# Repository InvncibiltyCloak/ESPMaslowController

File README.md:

# ESPMaslowController
Upgrade of the Maslow CNC controller based on the ESP32 microcontroller.

The design files are for KiCAD.

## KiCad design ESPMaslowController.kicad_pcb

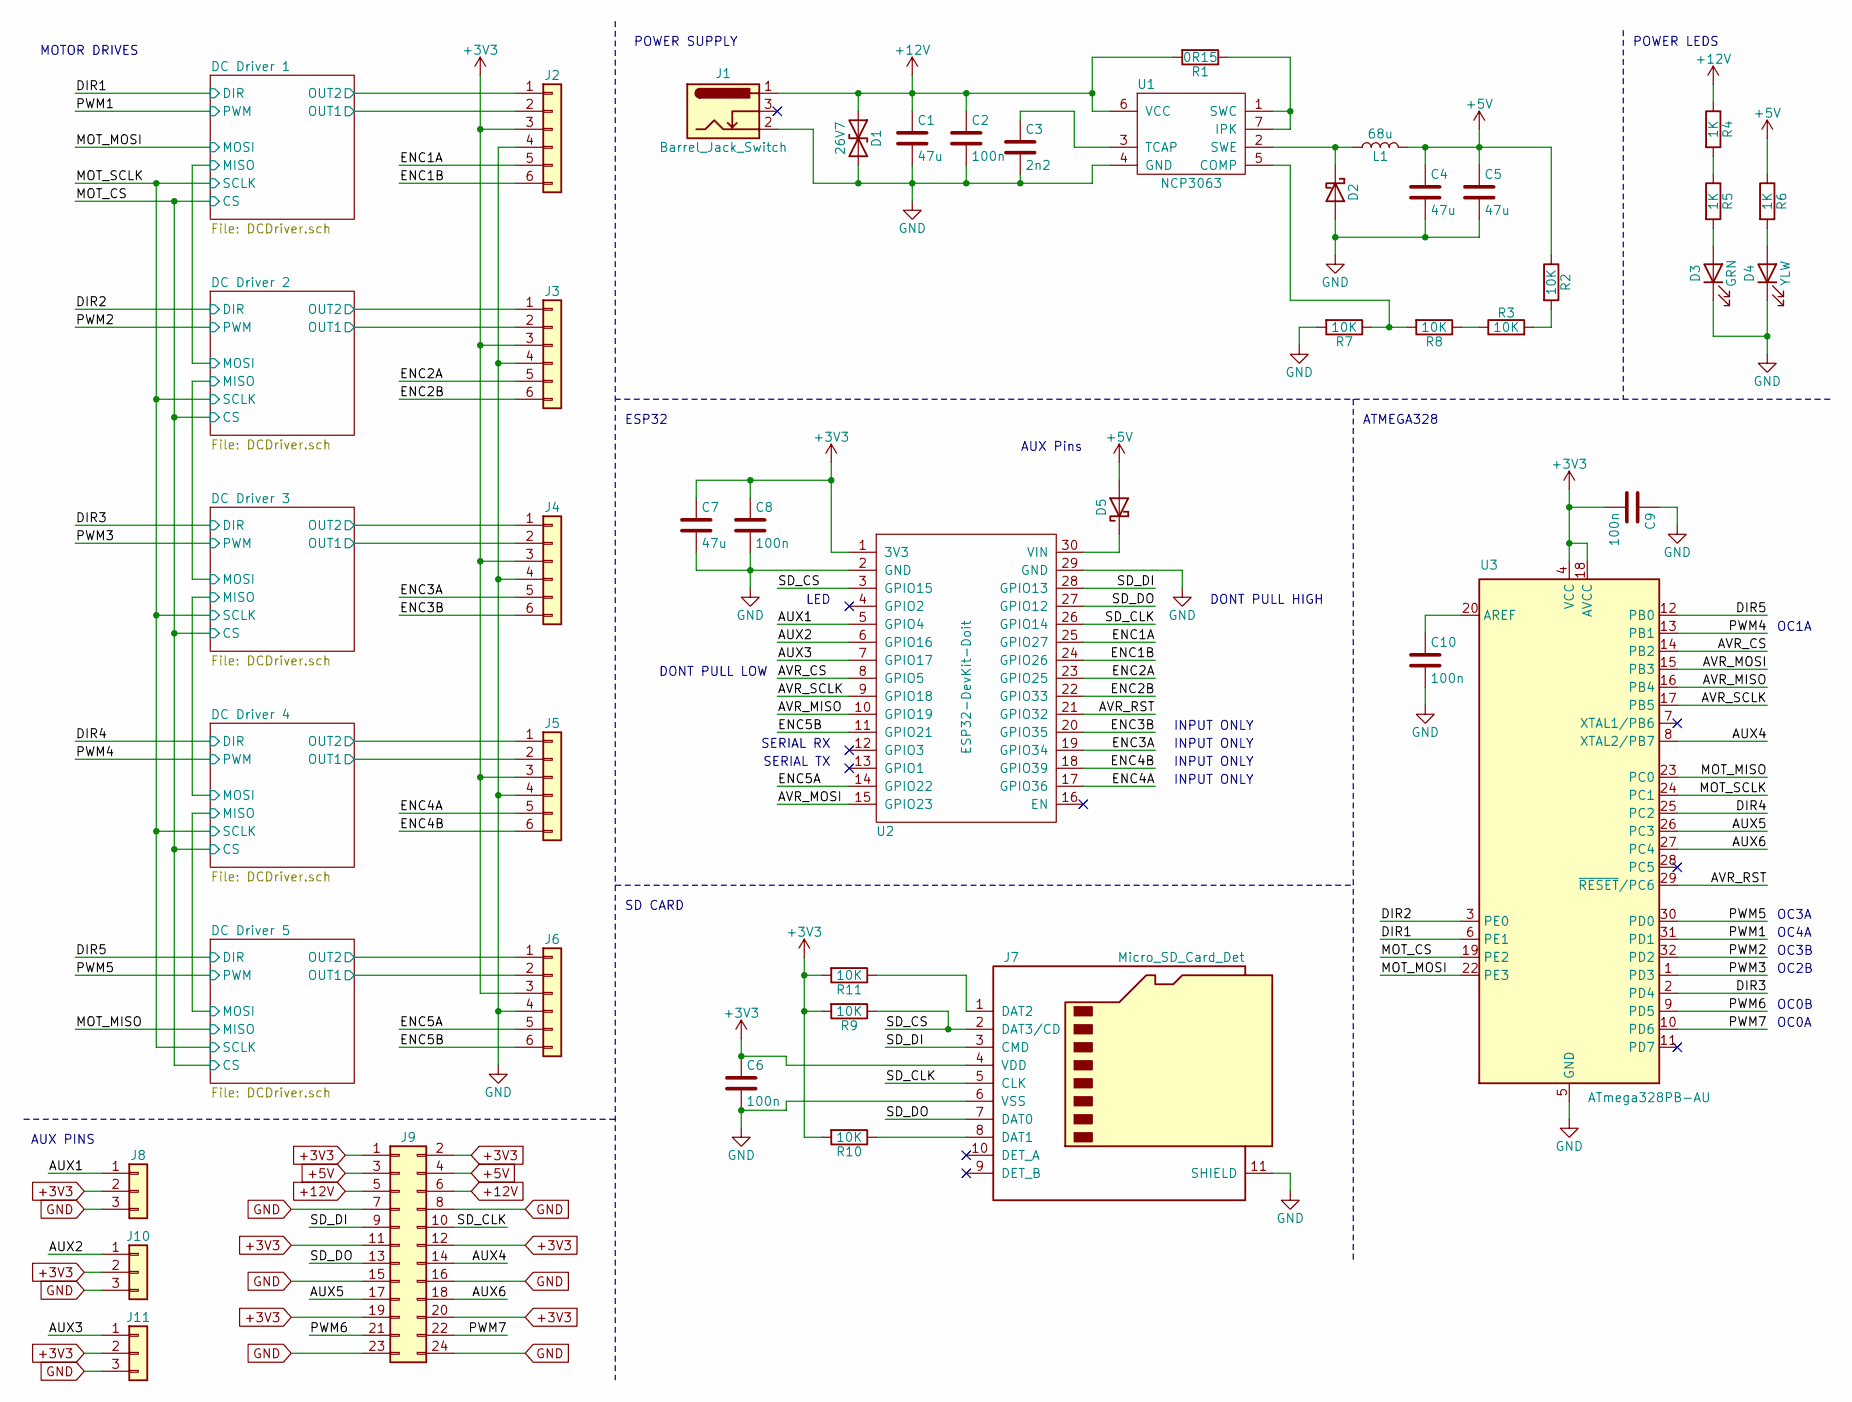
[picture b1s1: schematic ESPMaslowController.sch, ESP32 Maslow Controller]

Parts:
C1: 47u; CP_Elec_6.3x5.9; MPN 35SVPK47M
C2, C6, C8, C9, C10: 100n; C_0805_2012Metric; MPN CC0805KRX7R9BB104; LCSC C49678
C3: 2n2; C_0805_2012Metric; MPN CL21B222KBANNNC; LCSC C28260
C4, C5, C7: 47u; C_1206_3216Metric; MPN CL31A476MQHNNNE; LCSC C96123
D1: 26V7; D_SMA; MPN SMAJ24CA
D2, D5: 2A; D_SMA; MPN STPS2L30A
D3: GRN; LED_0805_2012Metric_Castellated; MPN LTST-C170KGKT; LCSC C2297
D4: YLW; LED_0805_2012Metric_Castellated; MPN LTST-C171KSKT; LCSC C2296
J1: Barrel_Jack_Switch; BarrelJack_CUI_PJ-036AH-SMT_Horizontal; MPN PJ-036AH-SMT-TR
J2, J3, J4, J5, J6: B6B-XH-A; JST_XH_B6B-XH-A_1x06_P2.50mm_Vertical; MPN B6B-PH-K-S(LF)(SN)
J7: Micro_SD_Card_Det; microSD_HC_Hirose_DM3AT-SF-PEJM5; MPN DM3AT-SF-PEJM5
J8, J10, J11: Conn_01x03; PinHeader_1x03_P2.54mm_Vertical; MPN G800W305018EU
J9: Conn_02x12_Odd_Even; PinHeader_2x12_P2.54mm_Vertical; MPN G800W590018EU
L1: 68u; L_12x12mm_H8mm; MPN NS12575T680MN
R1: 0R15; R_0805_2012Metric; MPN KDV08FR150ET
R2, R3, R7, R8, R9, R10, R11: 10K; R_0805_2012Metric; MPN RC0805FR-0710KL; LCSC C17414
R4, R5, R6: 1K; R_0805_2012Metric; MPN RC0805FR-071KL; LCSC C17513
U1: NCP3063; SO-8_3.9x4.9mm_P1.27mm; MPN NCP3063BDR2G
U2: ESP32-DevKit-Doit; ESP32-DEVKIT-V1; MPN ESP32 DevKit v1
U3: ATmega328PB-AU; TQFP-32_7x7mm_P0.8mm; MPN ATMEGA328PB-AU

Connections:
+3V3: C6.1, C7.1, C8.1, C9.2, J2.3, J3.3, J4.3, J5.3, J6.3, J7.4 (VDD), J8.2, J9.1, J9.2, J9.11, J9.12, J9.19, J9.20, J10.2, J11.2, R9.2, R10.2, R11.2, U2.1 (3V3), U3.4 (VCC), U3.18 (AVCC); also elsewhere on the board
+5V: C4.1, C5.1, D5.2 (A), J9.3, J9.4, L1.1, R2.1, R6.1
+12V: C1.1, C2.1, D1.1 (A1), J1.1, J9.5, J9.6, R1.2, R4.1, U1.6 (VCC); also elsewhere on the board
/AUX1: J8.1, U2.5 (GPIO4)
/AUX2: J10.1, U2.6 (GPIO16)
/AUX3: J11.1, U2.7 (GPIO17)
/AUX4: J9.14, U3.8 (XTAL2/PB7)
/AUX5: J9.17, U3.26 (PC3)
/AUX6: J9.18, U3.27 (PC4)
/AVR_CS: U2.8 (GPIO5), U3.14 (PB2)
/AVR_MISO: U2.10 (GPIO19), U3.16 (PB4)
/AVR_MOSI: U2.15 (GPIO23), U3.15 (PB3)
/AVR_RST: U2.21 (GPIO32), U3.29 (~RESET~/PC6)
/AVR_SCLK: U2.9 (GPIO18), U3.17 (PB5)
/DC Driver 1/OUT1: J2.2; also elsewhere on the board
/DC Driver 1/OUT2: J2.1; also elsewhere on the board
/DC Driver 2/OUT1: J3.2; also elsewhere on the board
/DC Driver 2/OUT2: J3.1; also elsewhere on the board
/DC Driver 3/OUT1: J4.2; also elsewhere on the board
/DC Driver 3/OUT2: J4.1; also elsewhere on the board
/DC Driver 4/OUT1: J5.2; also elsewhere on the board
/DC Driver 4/OUT2: J5.1; also elsewhere on the board
/DC Driver 5/OUT1: J6.2; also elsewhere on the board
/DC Driver 5/OUT2: J6.1; also elsewhere on the board
/DIR1: U3.6 (PE1); also elsewhere on the board
/DIR2: U3.3 (PE0); also elsewhere on the board
/DIR3: U3.2 (PD4); also elsewhere on the board
/DIR4: U3.25 (PC2); also elsewhere on the board
/DIR5: U3.12 (PB0); also elsewhere on the board
/ENC1A: J2.5, U2.25 (GPIO27)
/ENC1B: J2.6, U2.24 (GPIO26)
/ENC2A: J3.5, U2.23 (GPIO25)
/ENC2B: J3.6, U2.22 (GPIO33)
/ENC3A: J4.5, U2.19 (GPIO34)
/ENC3B: J4.6, U2.20 (GPIO35)
/ENC4A: J5.5, U2.17 (GPIO36)
/ENC4B: J5.6, U2.18 (GPIO39)
/ENC5A: J6.5, U2.14 (GPIO22)
/ENC5B: J6.6, U2.11 (GPIO21)
/MOT_CS: U3.19 (PE2); also elsewhere on the board
/MOT_MISO: U3.23 (PC0); also elsewhere on the board
/MOT_MOSI: U3.22 (PE3); also elsewhere on the board
/MOT_SCLK: U3.24 (PC1); also elsewhere on the board
/PWM1: U3.31 (PD1); also elsewhere on the board
/PWM2: U3.32 (PD2); also elsewhere on the board
/PWM3: U3.1 (PD3); also elsewhere on the board
/PWM4: U3.13 (PB1); also elsewhere on the board
/PWM5: U3.30 (PD0); also elsewhere on the board
/PWM6: J9.21, U3.9 (PD5)
/PWM7: J9.22, U3.10 (PD6)
/SD_CLK: J7.5 (CLK), J9.10, U2.26 (GPIO14)
/SD_CS: J7.2 (DAT3/CD), R9.1, U2.3 (GPIO15)
/SD_DI: J7.3 (CMD), J9.9, U2.28 (GPIO13)
/SD_DO: J7.7 (DAT0), J9.13, U2.27 (GPIO12)
GND: C1.2, C2.2, C3.2, C4.2, C5.2, C6.2, C7.2, C8.2, C9.1, C10.2, D1.2 (A2), D2.2 (A), D3.1 (K), D4.1 (K), J1.2, J2.4, J3.4, J4.4, J5.4, J6.4, J7.6 (VSS), J7.11 (SHIELD), J8.3, J9.7, J9.8, J9.15, J9.16, J9.23, J9.24, J10.3, J11.3, R7.2, U1.4 (GND), U2.2 (GND), U2.29 (GND), U3.5 (GND), U3.21 (GND); also elsewhere on the board
unnamed: C3.1, U1.3 (TCAP)
unnamed: C10.1, U3.20 (AREF)
unnamed: D2.1 (K), L1.2, U1.2 (SWE)
unnamed: D3.2 (A), R5.2
unnamed: D4.2 (A), R6.2
unnamed: D5.1 (K), U2.30 (VIN)
unnamed: J7.1 (DAT2), R11.1
unnamed: J7.8 (DAT1), R10.1
unnamed: R1.1, U1.1 (SWC), U1.7 (IPK)
unnamed: R2.2, R3.2
unnamed: R3.1, R8.1
unnamed: R4.2, R5.1
unnamed: R7.1, R8.2, U1.5 (COMP)

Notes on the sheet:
AUX Pins
SERIAL TX
DONT PULL LOW
INPUT ONLY
SERIAL RX
LED
DONT PULL HIGH
AUX PINS
MOTOR DRIVES
POWER SUPPLY
POWER LEDS
ESP32
ATMEGA328
SD CARD
OC2B
OC0B
OC0A
OC1A
OC3A
OC4A
OC3B

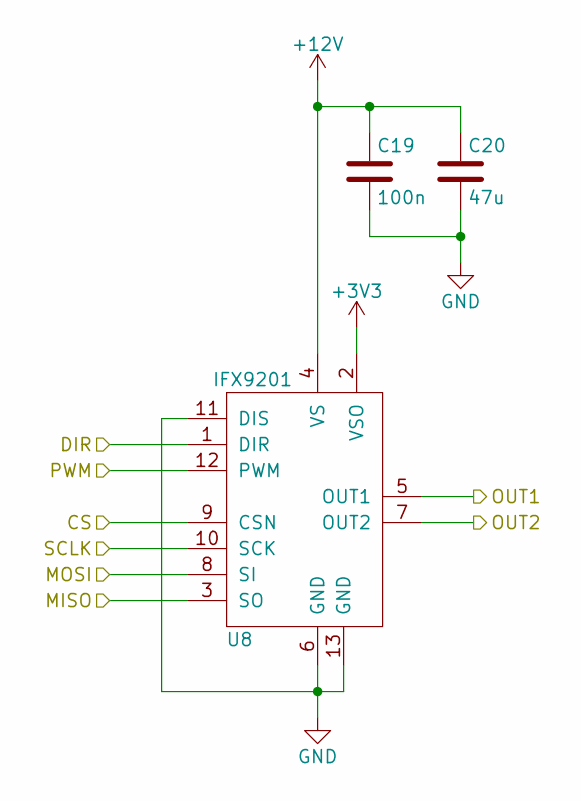
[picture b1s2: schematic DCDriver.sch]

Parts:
C11: 100n; C_0805_2012Metric; MPN CC0805KRX7R9BB104; LCSC C49678
C12: 47u; CP_Elec_6.3x5.9; MPN 35SVPK47M
U4: IFX9201; Infineon_PG-DSO-12-9_ThermalVias; MPN IFX9201SGAUMA1; LCSC C112633

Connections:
+3V3: U4.2 (VSO); also elsewhere on the board
+12V: C11.1, C12.1, U4.4 (VS); also elsewhere on the board
/DC Driver 1/MISO: U4.3 (SO); also elsewhere on the board
/DC Driver 1/OUT1: U4.5 (OUT1); also elsewhere on the board
/DC Driver 1/OUT2: U4.7 (OUT2); also elsewhere on the board
/DIR1: U4.1 (DIR); also elsewhere on the board
/MOT_CS: U4.9 (CSN); also elsewhere on the board
/MOT_MOSI: U4.8 (SI); also elsewhere on the board
/MOT_SCLK: U4.10 (SCK); also elsewhere on the board
/PWM1: U4.12 (PWM); also elsewhere on the board
GND: C11.2, C12.2, U4.6 (GND), U4.11 (DIS), U4.13 (GND); also elsewhere on the board

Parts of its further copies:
C13, C15, C17, C19: 100n; C_0805_2012Metric; MPN CC0805KRX7R9BB104; LCSC C49678
C14, C16, C18, C20: 47u; CP_Elec_6.3x5.9; MPN 35SVPK47M
U5, U6, U7, U8: IFX9201; Infineon_PG-DSO-12-9_ThermalVias; MPN IFX9201SGAUMA1; LCSC C112633

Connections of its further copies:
+3V3: U5.2 (VSO), U6.2 (VSO), U7.2 (VSO), U8.2 (VSO); also elsewhere on the board
+12V: C13.1, C14.1, C15.1, C16.1, C17.1, C18.1, C19.1, C20.1, U5.4 (VS), U6.4 (VS), U7.4 (VS), U8.4 (VS); also elsewhere on the board
/DC Driver 1/MISO: U5.8 (SI); also elsewhere on the board
/DC Driver 2/MISO: U5.3 (SO), U6.8 (SI)
/DC Driver 2/OUT1: U5.5 (OUT1); also elsewhere on the board
/DC Driver 2/OUT2: U5.7 (OUT2); also elsewhere on the board
/DC Driver 3/MISO: U6.3 (SO), U7.8 (SI)
/DC Driver 3/OUT1: U6.5 (OUT1); also elsewhere on the board
/DC Driver 3/OUT2: U6.7 (OUT2); also elsewhere on the board
/DC Driver 4/MISO: U7.3 (SO), U8.8 (SI)
/DC Driver 4/OUT1: U7.5 (OUT1); also elsewhere on the board
/DC Driver 4/OUT2: U7.7 (OUT2); also elsewhere on the board
/DC Driver 5/OUT1: U8.5 (OUT1); also elsewhere on the board
/DC Driver 5/OUT2: U8.7 (OUT2); also elsewhere on the board
/DIR2: U5.1 (DIR); also elsewhere on the board
/DIR3: U6.1 (DIR); also elsewhere on the board
/DIR4: U7.1 (DIR); also elsewhere on the board
/DIR5: U8.1 (DIR); also elsewhere on the board
/MOT_CS: U5.9 (CSN), U6.9 (CSN), U7.9 (CSN), U8.9 (CSN); also elsewhere on the board
/MOT_MISO: U8.3 (SO); also elsewhere on the board
/MOT_SCLK: U5.10 (SCK), U6.10 (SCK), U7.10 (SCK), U8.10 (SCK); also elsewhere on the board
/PWM2: U5.12 (PWM); also elsewhere on the board
/PWM3: U6.12 (PWM); also elsewhere on the board
/PWM4: U7.12 (PWM); also elsewhere on the board
/PWM5: U8.12 (PWM); also elsewhere on the board
GND: C13.2, C14.2, C15.2, C16.2, C17.2, C18.2, C19.2, C20.2, U5.6 (GND), U5.11 (DIS), U5.13 (GND), U6.6 (GND), U6.11 (DIS), U6.13 (GND), U7.6 (GND), U7.11 (DIS), U7.13 (GND), U8.6 (GND), U8.11 (DIS), U8.13 (GND); also elsewhere on the board

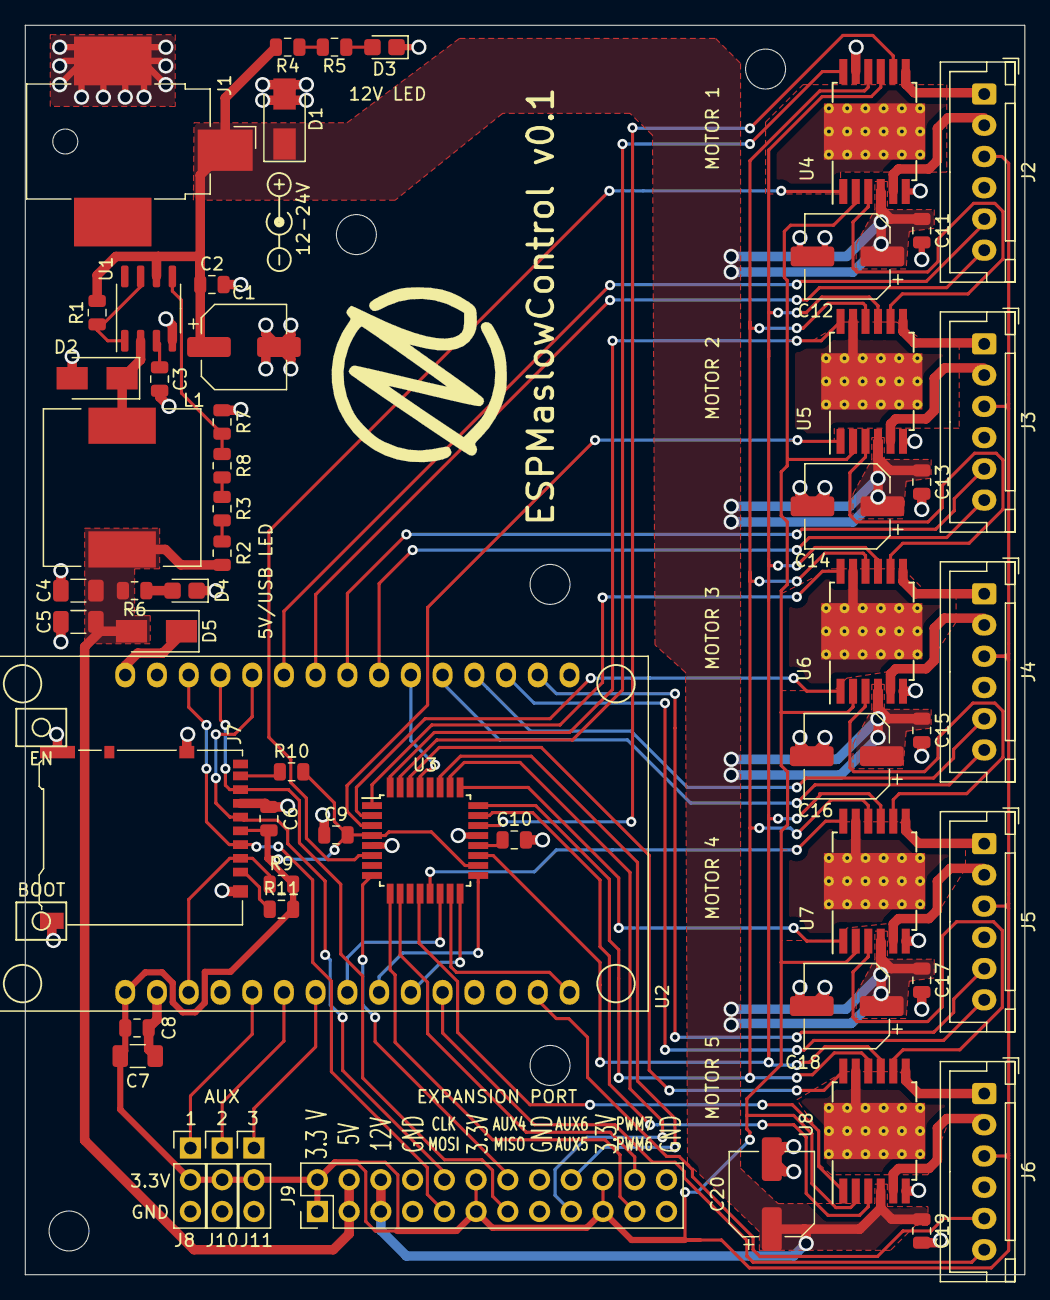
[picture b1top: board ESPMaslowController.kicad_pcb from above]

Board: 2 copper layers, 80.0 x 100.0 mm, 56 parts (0 on the bottom side), 72 nets.

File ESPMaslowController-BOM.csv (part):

Reference, Value, Footprint, Datasheet, BuyLink, MFR, MPN, Price, LCSC
"U2","ESP32-DevKit-Doit","ProjectFootprints:ESP32-DEVKIT-V1","","https://www.aliexpress.com/item/4000111107743.html","Espressif","ESP32 DevKit v1","6.00",""
"J1","Barrel_Jack_Switch","Connector_BarrelJack:BarrelJack_CUI_PJ-036AH-SMT_Horizontal","https://www.cuidevices.com/product/resource/digikeypdf/pj-03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","","CUI","PJ-036AH-SMT-TR","1.36",""
"J7","Micro_SD_Card_Det","Connector_Card:microSD_HC_Hirose_DM3AT-SF-PEJM5","https://www.hirose.com/product/document?clcode=CL0609-0033-6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","","HRS","DM3AT-SF-PEJM5","2.50",""
"C6","100n","Capacitor_SMD:C_0805_2012Metric","https://www.yageo.com/upload/media/product/productsearch/dat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","","Yageo","CC0805KRX7R9BB104","0.046","C49678"
"C8","100n","Capacitor_SMD:C_0805_2012Metric","https://www.yageo.com/upload/media/product/productsearch/dat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","","Yageo","CC0805KRX7R9BB104","0.046","C49678"
"C2","100n","Capacitor_SMD:C_0805_2012Metric","https://www.yageo.com/upload/media/product/productsearch/dat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","","Yageo","CC0805KRX7R9BB104","0.046","C49678"
"C1","47u","Capacitor_SMD:CP_Elec_6.3x5.9","https://industrial.panasonic.com/cdbs/www-data/pdf/AAB8000/A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","","Panasonic","35SVPK47M","0.713",""
"U1","NCP3063","Package_SO:SO-8_3.9x4.9mm_P1.27mm","http://www.onsemi.com/pub/Collateral/NCP3063-D.PDF","","ONSemi","NCP3063BDR2G","0.99",""
"C3","2n2","Capacitor_SMD:C_0805_2012Metric","http://www.samsungsem.com/kr/support/product-search/mlcc/CL2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","","Samsung","CL21B222KBANNNC","0.10","C28260"
"R1","0R15","Resistor_SMD:R_0805_2012Metric","https://www.ohmite.com/assets/docs/res_kdv.pdf?r=false","","Ohmite","KDV08FR150ET","0.29",""
"R2","10K","Resistor_SMD:R_0805_2012Metric","https://www.yageo.com/upload/media/product/productsearch/dat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","","Yageo","RC0805FR-0710KL","0.10","C17414"
"L1","68u","Inductor_SMD:L_12x12mm_H8mm","https://ds.yuden.co.jp/TYCOMPAS/ut/detail?pn=NS12575T680MN%20&u=M","","Taiyo Yuden","NS12575T680MN","1.47",""
"D2","2A","Diode_SMD:D_SMA","https://datasheet.lcsc.com/szlcsc/STMicroelectronics-STPS2L3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","","STMicro","STPS2L30A","0.43",""
"C4","47u","Capacitor_SMD:C_1206_3216Metric","https://media.digikey.com/pdf/Data%20Sheets/Samsung%20PDFs/C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","","Samsung","CL31A476MQHNNNE","0.33","C96123"
"C5","47u","Capacitor_SMD:C_1206_3216Metric","https://media.digikey.com/pdf/Data%20Sheets/Samsung%20PDFs/C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","","Samsung","CL31A476MQHNNNE","0.33","C96123"
"C7","47u","Capacitor_SMD:C_1206_3216Metric","https://media.digikey.com/pdf/Data%20Sheets/Samsung%20PDFs/C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","","Samsung","CL31A476MQHNNNE","0.33","C96123"
"J2","B6B-PH-K-S","Connector_JST:JST_PH_B6B-PH-K_1x06_P2.00mm_Vertical","http://www.jst-mfg.com/product/pdf/eng/ePH.pdf","","JST","B6B-PH-K-S(LF)(SN)","0.33",""
"J3","B6B-PH-K-S","Connector_JST:JST_PH_B6B-PH-K_1x06_P2.00mm_Vertical","http://www.jst-mfg.com/product/pdf/eng/ePH.pdf","","JST","B6B-PH-K-S(LF)(SN)","0.33",""
"J4","B6B-PH-K-S","Connector_JST:JST_PH_B6B-PH-K_1x06_P2.00mm_Vertical","http://www.jst-mfg.com/product/pdf/eng/ePH.pdf","","JST","B6B-PH-K-S(LF)(SN)","0.33",""
"D5","2A","Diode_SMD:D_SMA","https://datasheet.lcsc.com/szlcsc/STMicroelectronics-STPS2L3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","","STMicro","STPS2L30A","0.43",""
"D3","GRN","LED_SMD:LED_0805_2012Metric_Castellated","http://optoelectronics.liteon.com/upload/download/DS22-2000-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","","Lite-On","LTST-C170KGKT","0.35","C2297"
"R5","1K","Resistor_SMD:R_0805_2012Metric","https://www.yageo.com/upload/media/product/productsearch/dat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","","Yageo","RC0805FR-071KL","0.10","C17513"
"R4","1K","Resistor_SMD:R_0805_2012Metric","https://www.yageo.com/upload/media/product/productsearch/dat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","","Yageo","RC0805FR-071KL","0.10","C17513"
"D4","YLW","LED_SMD:LED_0805_2012Metric_Castellated","http://optoelectronics.liteon.com/upload/download/DS22-2000-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","","Lite-On","LTST-C171KSKT","0.31","C2296"
"R6","1K","Resistor_SMD:R_0805_2012Metric","https://www.yageo.com/upload/media/product/productsearch/dat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","","Yageo","RC0805FR-071KL","0.10","C17513"
"U3","ATmega328PB-AU","Package_QFP:TQFP-32_7x7mm_P0.8mm","http://ww1.microchip.com/downloads/en/DeviceDoc/40001906C.pdf","","Microchip","ATMEGA328PB-AU","1.34",""
"J5","B6B-PH-K-S","Connector_JST:JST_PH_B6B-PH-K_1x06_P2.00mm_Vertical","http://www.jst-mfg.com/product/pdf/eng/ePH.pdf","","JST","B6B-PH-K-S(LF)(SN)","0.33",""
"J6","B6B-PH-K-S","Connector_JST:JST_PH_B6B-PH-K_1x06_P2.00mm_Vertical","http://www.jst-mfg.com/product/pdf/eng/ePH.pdf","","JST","B6B-PH-K-S(LF)(SN)","0.33",""
"C10","100n","Capacitor_SMD:C_0805_2012Metric","https://www.yageo.com/upload/media/product/productsearch/dat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","","Yageo","CC0805KRX7R9BB104","0.046","C49678"
"C9","100n","Capacitor_SMD:C_0805_2012Metric","https://www.yageo.com/upload/media/product/productsearch/dat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","","Yageo","CC0805KRX7R9BB104","0.046","C49678"
"D1","26V7","Diode_SMD:D_SMA","https://www.littelfuse.com/~/media/electronics/datasheets/tv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","","LittelFuse","SMAJ24CA","0.35",""
"R3","10K","Resistor_SMD:R_0805_2012Metric","https://www.yageo.com/upload/media/product/productsearch/dat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","","Yageo","RC0805FR-0710KL","0.10","C17414"
"R8","10K","Resistor_SMD:R_0805_2012Metric","https://www.yageo.com/upload/media/product/productsearch/dat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","","Yageo","RC0805FR-0710KL","0.10","C17414"
"R7","10K","Resistor_SMD:R_0805_2012Metric","https://www.yageo.com/upload/media/product/productsearch/dat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","","Yageo","RC0805FR-0710KL","0.10","C17414"
"J9","Conn_02x12_Odd_Even","Connector_PinHeader_2.54mm:PinHeader_2x12_P2.54mm_Vertical","http://www.amphenol-icc.com/media/wysiwyg/files/drawing/g800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","","Amphenol","G800W590018EU","0.23",""
"J8","Conn_01x03","Connector_PinHeader_2.54mm:PinHeader_1x03_P2.54mm_Vertical","http://www.amphenol-icc.com/media/wysiwyg/files/drawing/g800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","","Amphenol","G800W305018EU","0.10",""
"J10","Conn_01x03","Connector_PinHeader_2.54mm:PinHeader_1x03_P2.54mm_Vertical","http://www.amphenol-icc.com/media/wysiwyg/files/drawing/g800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","","Amphenol","G800W305018EU","0.10",""
"J11","Conn_01x03","Connector_PinHeader_2.54mm:PinHeader_1x03_P2.54mm_Vertical","http://www.amphenol-icc.com/media/wysiwyg/files/drawing/g800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","","Amphenol","G800W305018EU","0.10",""
"U4","IFX9201","Package_SO:Infineon_PG-DSO-12-9_ThermalVias","https://www.infineon.com/dgdl/Infineon-IFX9201SG-DS-v01_01-E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","","Infineon","IFX9201SGAUMA1 ","3.55","C112633"
"C11","100n","Capacitor_SMD:C_0805_2012Metric","https://www.yageo.com/upload/media/product/productsearch/dat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","","Yageo","CC0805KRX7R9BB104","0.046","C49678"
"C12","47u","Capacitor_SMD:CP_Elec_6.3x5.9","https://industrial.panasonic.com/cdbs/www-data/pdf/AAB8000/A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","","Panasonic","35SVPK47M","0.713",""
"U5","IFX9201","Package_SO:Infineon_PG-DSO-12-9_ThermalVias","https://www.infineon.com/dgdl/Infineon-IFX9201SG-DS-v01_01-E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","","Infineon","IFX9201SGAUMA1 ","3.55","C112633"
"C13","100n","Capacitor_SMD:C_0805_2012Metric","https://www.yageo.com/upload/media/product/productsearch/dat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","","Yageo","CC0805KRX7R9BB104","0.046","C49678"
"C14","47u","Capacitor_SMD:CP_Elec_6.3x5.9","https://industrial.panasonic.com/cdbs/www-data/pdf/AAB8000/A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","","Panasonic","35SVPK47M","0.713",""
"U6","IFX9201","Package_SO:Infineon_PG-DSO-12-9_ThermalVias","https://www.infineon.com/dgdl/Infineon-IFX9201SG-DS-v01_01-E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","","Infineon","IFX9201SGAUMA1 ","3.55","C112633"
"C15","100n","Capacitor_SMD:C_0805_2012Metric","https://www.yageo.com/upload/media/product/productsearch/dat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","","Yageo","CC0805KRX7R9BB104","0.046","C49678"
"C16","47u","Capacitor_SMD:CP_Elec_6.3x5.9","https://industrial.panasonic.com/cdbs/www-data/pdf/AAB8000/A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","","Panasonic","35SVPK47M","0.713",""
"U7","IFX9201","Package_SO:Infineon_PG-DSO-12-9_ThermalVias","https://www.infineon.com/dgdl/Infineon-IFX9201SG-DS-v01_01-E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","","Infineon","IFX9201SGAUMA1 ","3.55","C112633"
"C17","100n","Capacitor_SMD:C_0805_2012Metric","https://www.yageo.com/upload/media/product/productsearch/dat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","","Yageo","CC0805KRX7R9BB104","0.046","C49678"
"C18","47u","Capacitor_SMD:CP_Elec_6.3x5.9","https://industrial.panasonic.com/cdbs/www-data/pdf/AAB8000/A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","","Panasonic","35SVPK47M","0.713",""
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
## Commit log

2020-10-02 First revision of schematic complete.
2020-10-03 Moved PWM outputs to OC pins on ATmega328.
    The original plan was to do a software PWM on Port D. Testing showed frequencies of only 450 Hz could be achieved at 100% CPU usage. This is too low to be useful, and was not phase-correct PWM.
2020-10-04 Finalized BOM and reworked AUX pins.
2020-10-04 Created footprint for ESP32.
2020-10-08 Revision v0.1 of PCB fully complete.
2020-10-09 Updated LCSC references to match ordered parts.
2020-10-09 Added some part numbers for the pin headers.
2020-10-09 Added a BOM to the project for easy reference.
    To guarantee the BOM is up-to-date, you can run the BOM generation script in KiCAD, although I will try to keep it up-to-date.
2020-10-12 Added pullups to unused SD card lines.
2020-10-12 Added pullup to SD CS line.
2020-12-19 Fixed board errors.
    Corrected motor connectors to be JST XH series (2.5 mm pitch).
    Corrected NCP3063 feedback resistor divider for 5V output.
2020-12-19 Updated README to have board render
